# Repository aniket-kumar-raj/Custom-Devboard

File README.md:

# Custom-Devboard
Story of Creation of My first Devboard

# My RP2040 Devboard Journal
**Author:** Aniket Kumar Raj
**Project:** Custom RP2040 Development Board
**System:** Windows 7 (32-bit)

---

## Log: Jan 8, 2026 - Setting up the Environment

### What I did today:
* **Research:** Read through the [Hack Club Blueprint Devboard guide](https://blueprint.hackclub.com/starter-projects/devboard).
* **Environment Setup:** Realized my computer is running **Windows 7 32-bit**, which doesn't support the latest KiCad 8.0.
* **Problem Solving:** Found an archive of **KiCad 5.1.12 (i686)** which is compatible with 32-bit systems. 
* **Download:** Started downloading the full installer to ensure I have all the symbols and footprints for the RP2040.

### Challenges:
* Modern documentation for the RP2040 usually assumes you are using KiCad 7 or 8. I will have to adapt the steps (like finding the "Add Text" tool) to the older KiCad 5 interface.
* Ensuring the 32-bit version has the specific **RP2040 library**, as this chip was released after KiCad 5 was first made. I might need to import the library manually.

### Next Steps:
* Finish the installation of KiCad 5.1.12.
* Start a new project and begin the **Schematic** (Eeschema).
* Map out the power circuit (5V to 3.3V) and the USB-C data lines.
* **Goal:** Get my name on the Silkscreen layer of the PCB layout!

---

## Hardware Specifications
* **MCU:** RP2040
* **Storage:** 16MB Flash (W25Q128)
* **Connectivity:** USB-C
* **Custom Feature:** Custom Silkscreen branding and a unique PCB shape.

# Engineering Journal: RP2040 PCB Project

## [2026-01-09] - BOM Optimization & Component Validation

### Summary
Today’s focus was on a deep-clean of the Bill of Materials (BOM) for the RP2040 custom board. Major discrepancies were identified between the intended electrical values and the selected LCSC part numbers. All critical resistors, capacitors, and the flash memory chip were cross-verified against the JLCPCB assembly library to ensure first-time-right manufacturing.

### Technical Tasks & Updates
- **USB Data Line Calibration:**
  - Corrected R1 and R2 to **27Ω** (LCSC: **C17594**). 
  - *Previous error:* Found a 10kΩ/100Ω mismatch in the part numbers which would have caused USB communication failure.
- **USB-C Power Negotiation:**
  - Validated R3 and R4 as **5.1kΩ** (LCSC: **C26023**).
  - Ensured the footprint is **0805** to match the PCB pads (previously incorrectly set to 0402).
- **Flash Memory Selection:**
  - Finalized U3 (NOR Flash) as **W25Q128JVSIQ** (LCSC: **C97521**).
  - Confirmed 128Mb (16MB) capacity and SOIC-8-208mil package compatibility.
- **Status Indicator:**
  - Corrected R8 for the LED to **330Ω** (LCSC: **C17630**) to ensure visible brightness.

### BOM Checklist (Verified 0805 Parts)
| Designator | Value | LCSC Part # | Role |
| :--- | :--- | :--- | :--- |
| R1, R2 | 27Ω | C17594 | USB Differential Pair Termination |
| R3, R4 | 5.1kΩ | C26023 | USB-C Configuration Channel (CC) |
| R5, R7 | 10kΩ | C17414 | Pull-up Resistors |
| R6 | 1kΩ | C17513 | Signal Limiting |
| R8 | 330Ω | C17630 | LED Current Limiting |
| U3 | 16MB Flash | C97521 | Program Storage (Basic Part) |

### Next Steps
- [ ] Export the final BOM as a Comma-Separated CSV.
- [ ] Perform a 3D Preview check on JLCPCB for the **U1 (RP2040)** and **U3 (Flash)** orientation (Pin 1 alignment).
- [ ] Verify the **J1 (USB-C)** edge clearance to ensure cables can fully seat in the connector.
- [ ] Finalize the order for assembly.

---

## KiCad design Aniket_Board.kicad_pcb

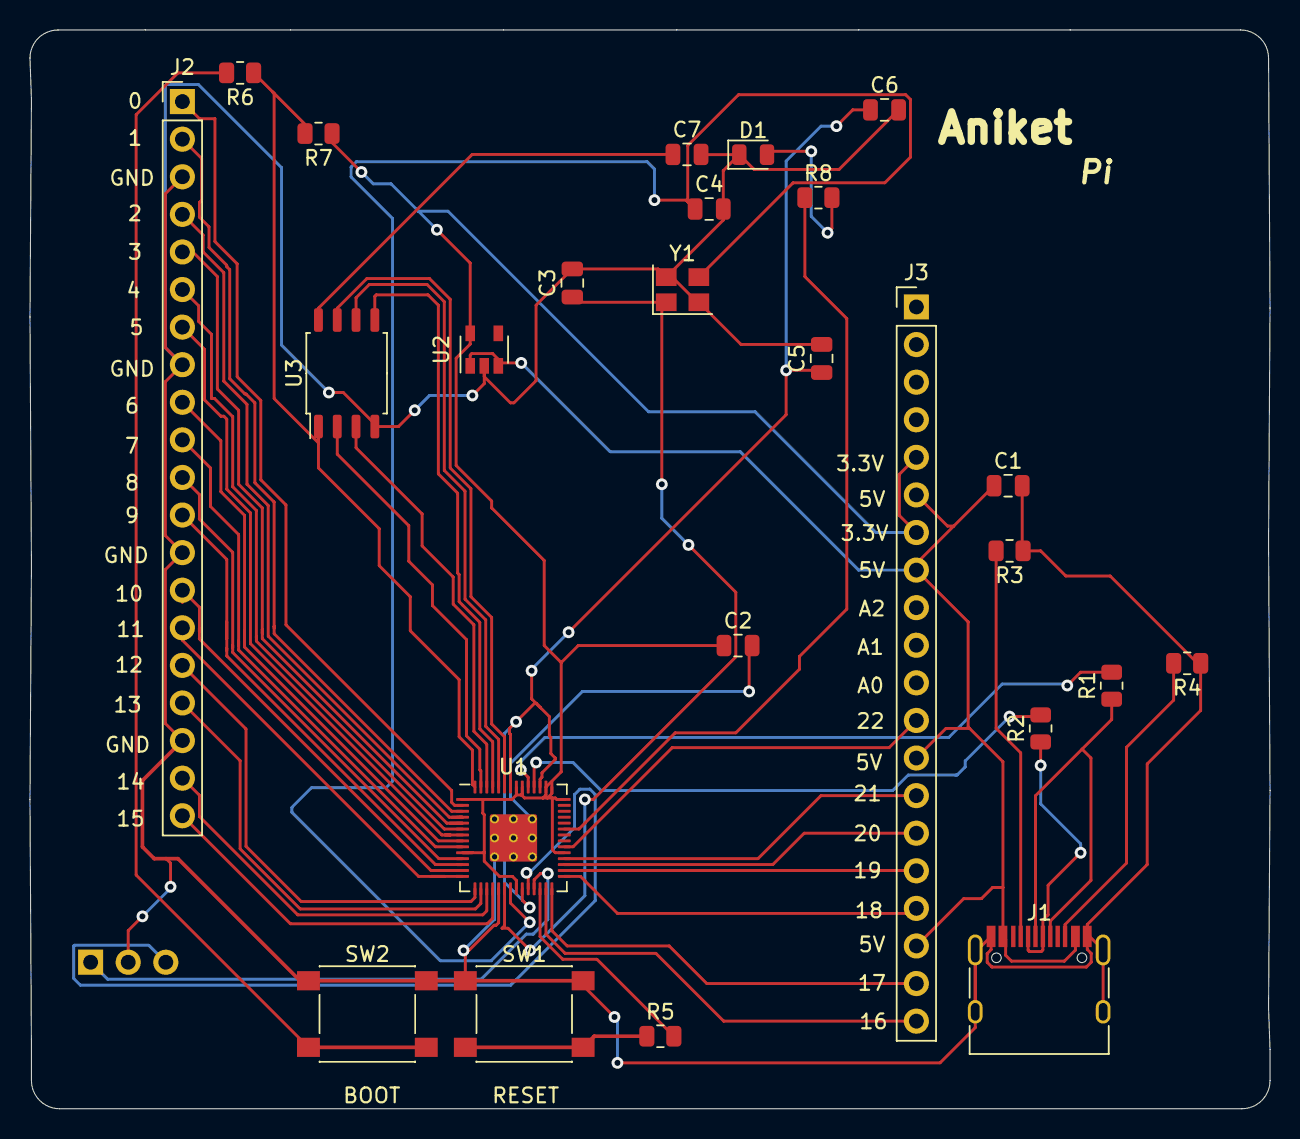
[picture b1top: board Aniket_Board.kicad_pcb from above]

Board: 2 copper layers, 83.8 x 72.9 mm, 26 parts (1 on the bottom side), 49 nets.

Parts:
C1, C2: 10uF; C_0805_2012Metric
C3, C4: 22pF; C_0805_2012Metric
C5, C6, C7: 0.1uF; C_0805_2012Metric
D1: LED; LED_0805_2012Metric
J1: USB_C_Receptacle_USB2.0; USB_C_Receptacle_HRO_TYPE-C-31-M-12
J2, J3: Conn_01x20_Male; PinHeader_1x20_P2.54mm_Vertical
J4: Conn_01x03_Male; PinHeader_1x03_P2.54mm_Horizontal
R1, R2: 27; R_0805_2012Metric
R3, R4: 5.1k; R_0805_2012Metric
R5, R7: 10k; R_0805_2012Metric
R6: 1k; R_0805_2012Metric
R8: 330ohm; R_0805_2012Metric
SW1: SW_Push; SW_SPST_PTS645
SW2: SW_Push boot; SW_SPST_PTS645
U1: RP2040; RP2040-QFN-56
U2: AP2112K-3.3; SOT-23-5
U3: Memory_Flash_W25Q128JVS; SOIC-8_5.23x5.23mm_P1.27mm
Y1: Crystal_GND24; Crystal_SMD_3225-4Pin_3.2x2.5mm

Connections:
/+3.3v: C2.1, J3.5, J3.7, R7.1, U1.1, U1.10, U1.22, U1.33, U1.42, U1.43, U1.44, U1.48, U1.49, U2.5
/+5v: C1.1, J1.A4, J1.A9, J1.B4, J1.B9, J3.6, J3.8, J3.13, J3.18, U2.1, U2.3
/D+: J1.A6, J1.B6, R1.1
/D-: J1.A7, J1.B7, R2.1
/GIO25: R8.1, U1.37
/GPIO0: J2.1, U1.2
/GPIO1: J2.2, U1.3
/GPIO2: J2.4, U1.4
/GPIO3: J2.5, U1.5
/GPIO4: J2.6, U1.6
/GPIO5: J2.7, U1.7
/GPIO6: J2.9, U1.8
/GPIO7: J2.10, U1.9
/GPIO8: J2.11, U1.11
/GPIO9: J2.12, U1.12
/GPIO10: J2.14, U1.13
/GPIO11: J2.15, U1.14
/GPIO12: J2.16, U1.15
/GPIO13: J2.17, U1.16
/GPIO14: J2.19, U1.17
/GPIO15: J2.20, U1.18
/GPIO16: J3.20, U1.27
/GPIO17: J3.19, U1.28
/GPIO18: J3.17, U1.29
/GPIO19: J3.16, U1.30
/GPIO20: J3.15, U1.31
/GPIO21: J3.14, U1.32
/GPIO22: J3.12, U1.34
/QSPI_SCLK: U1.52, U3.6
/QSPI_SD0: U1.53, U3.5
/QSPI_SD1: U1.55, U3.2
/QSPI_SD2: U1.54, U3.3
/QSPI_SD3: U1.51, U3.7
/QSPI_SS: R6.1, R7.2, U1.56, U3.1
/SWCLK: J4.3, U1.24
/SWD: J4.1, U1.25
/XIN: C3.1, U1.20, Y1.1
/XOUT: C4.1, U1.21, Y1.3
GND: C1.2, C2.2, C3.2, C4.2, C5.2, C6.2, C7.2, D1.1, J1.A1, J1.A12, J1.B1, J1.B12, J1.S1, J2.3, J2.8, J2.13, J2.18, J4.2, R3.1, R4.1, SW1.1, SW2.1, U1.19, U1.57, U2.2, U3.4, Y1.2, Y1.4
unnamed: C5.1, C6.1, U1.23, U1.45, U1.50
unnamed: C7.1, U3.8
unnamed: D1.2, R8.2
unnamed: J1.A5, R3.2
unnamed: J1.B5, R4.2
unnamed: R1.2, U1.47
unnamed: R2.2, U1.46
unnamed: R5.1, SW1.2
unnamed: R5.2, U1.26
unnamed: R6.2, SW2.2

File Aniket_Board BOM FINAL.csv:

Designator,Value,Footprint,LCSC Part #
U1,RP2040,QFN-56,C2040
U3,W25Q128JVS,SOIC-8,C2852233
U2,AP2112K-3.3,SOT-23-5,C51118
Y1,12MHz Crystal,3225-4P,C9002
J1,USB-C,TYPE-C-31-M-12,C165948
"R1, R2",27ohm,805,C17408
"R3, R4",5.1k,805,C25917
"R5, R7",10k,805,C17414
"C5, C6, C7",0.1uF,805,C49678
"C1, C2",10uF,805,C15850
"C3, C4",22pF,805,C1804
"SW1, SW2",Push Button,PTS645,C318884
D1,LED,805,C2297 (Green)
R6,1k,805,C17513
R8,330ohm,805,C17630
